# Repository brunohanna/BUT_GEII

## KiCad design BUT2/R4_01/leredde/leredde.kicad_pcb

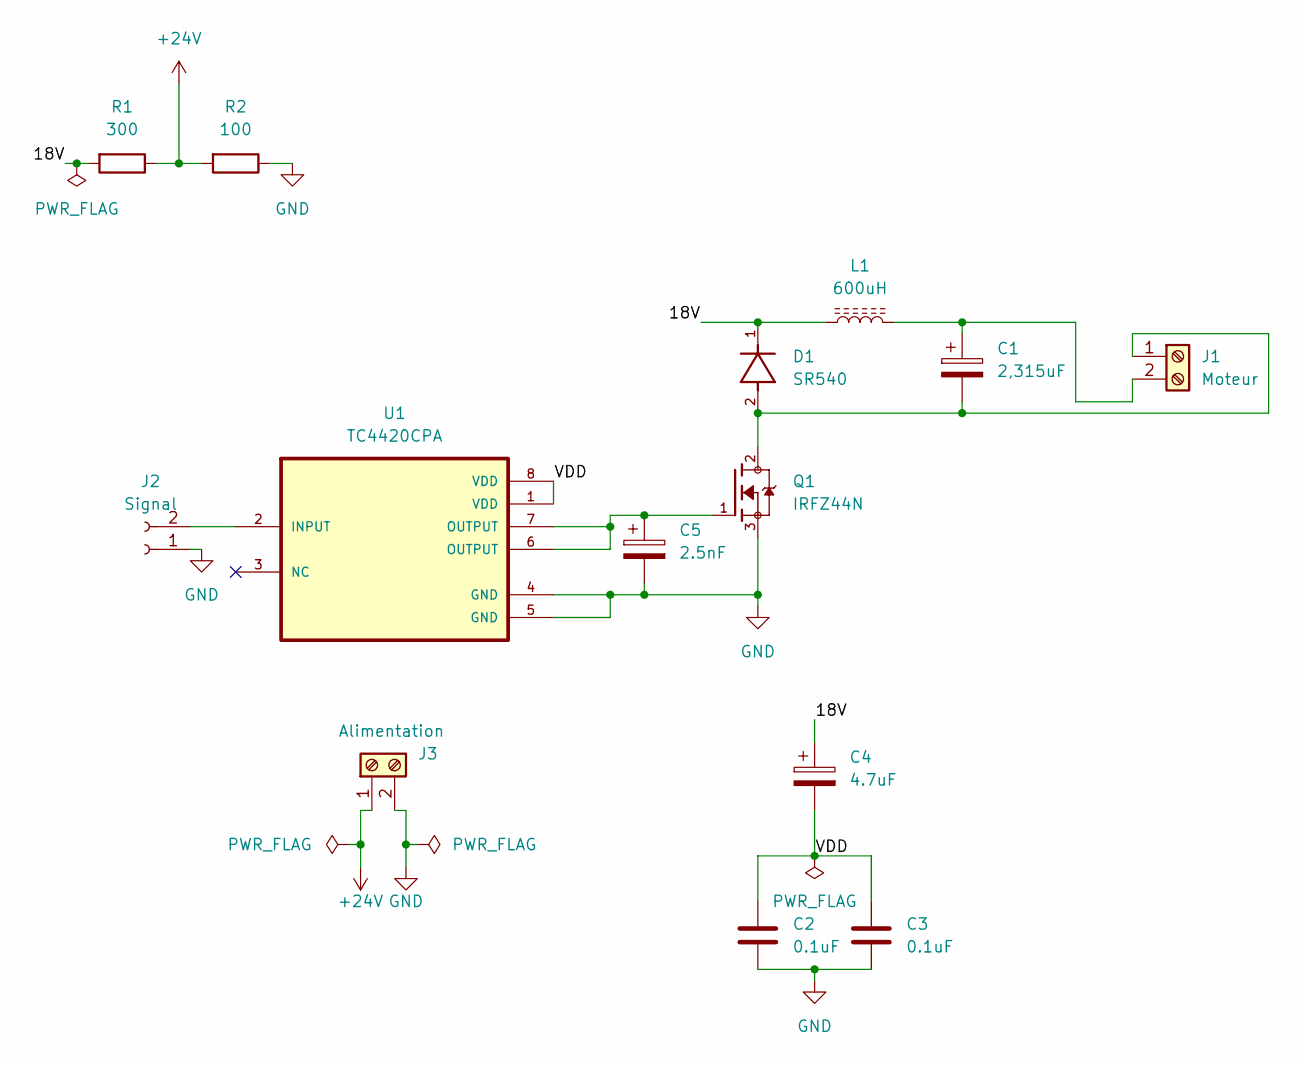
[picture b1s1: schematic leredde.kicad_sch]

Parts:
C1: 2,315uF; CP_Radial_D5.0mm_P2.50mm
C2, C3: 0.1uF; C_Rect_L7.0mm_W2.0mm_P5.00mm
C4: 4.7uF; CP_Radial_D5.0mm_P2.50mm
C5: 2.5nF; CP_Radial_D5.0mm_P2.50mm
D1: SR540; DO-241
J1: Moteur; TerminalBlock_bornier-2_P5.08mm
J2: Signal; PinSocket_1x02_P2.54mm_Vertical
J3: Alimentation; TerminalBlock_bornier-2_P5.08mm
L1: 600uH; L_Radial_D21.0mm_P19.00mm
Q1: IRFZ44N; TO254P1016X419X2286-3; PARTREV 09/21/10
R1: 300; R_Axial_DIN0207_L6.3mm_D2.5mm_P15.24mm_Horizontal
R2: 100; R_Axial_DIN0207_L6.3mm_D2.5mm_P15.24mm_Horizontal
U1: TC4420CPA; DIP-8_W7.62mm

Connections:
+24V: J3.1, R1.1, R2.2
/18V: C4.1, D1.1, L1.1, R1.2
/VDD: C2.1, C3.1, C4.2, U1.1 (VDD), U1.8 (VDD)
GND: C2.2, C3.2, C5.2, J2.1, J3.2, Q1.3, R2.1, U1.4 (GND), U1.5 (GND)
unnamed: C5.1, Q1.1, U1.6 (OUTPUT), U1.7 (OUTPUT)
unnamed: C1.2, D1.2, J1.1, Q1.2
unnamed: C1.1, J1.2, L1.2
unnamed: J2.2, U1.2 (INPUT)

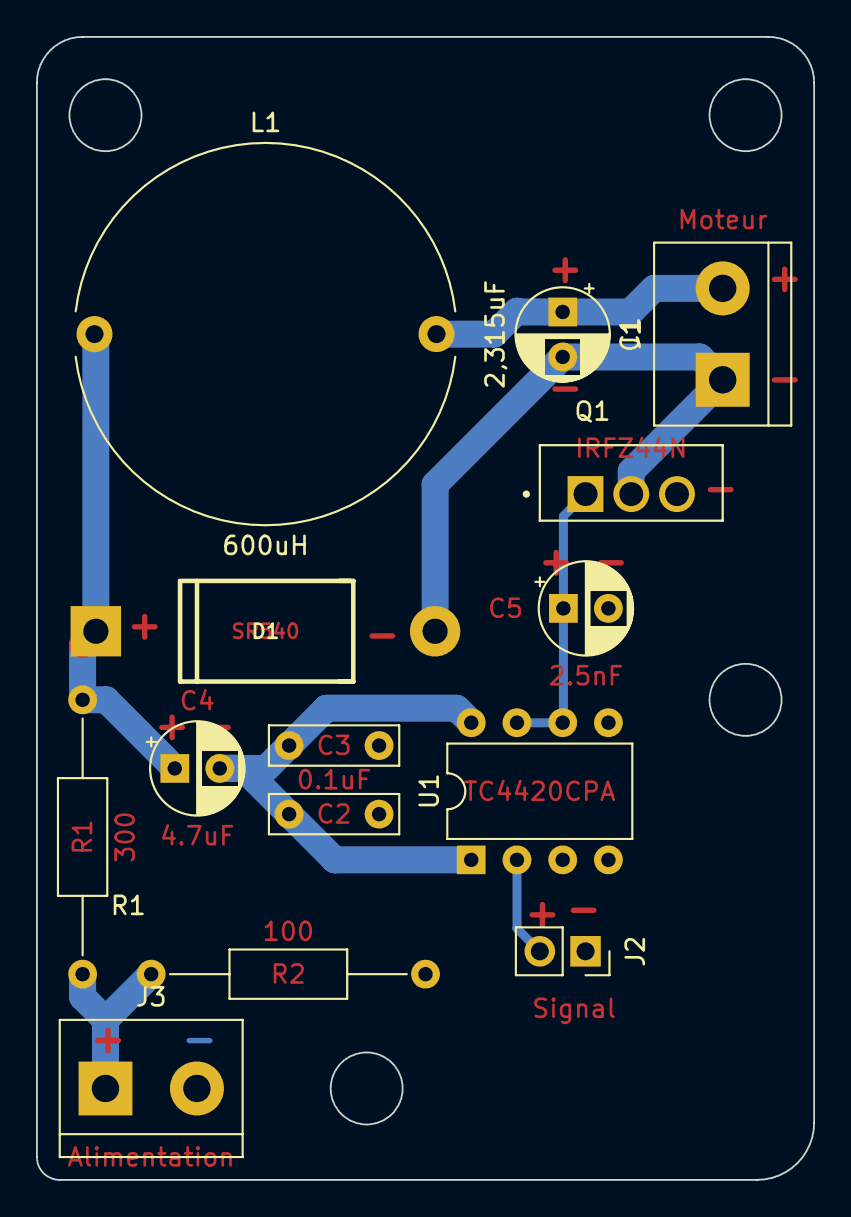
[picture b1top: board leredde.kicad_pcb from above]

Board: 2 copper layers, 43.2 x 63.5 mm, 14 parts (0 on the bottom side), 8 nets.

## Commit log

2025-01-27 BUT GEII
2025-02-01 Correction Leredde
